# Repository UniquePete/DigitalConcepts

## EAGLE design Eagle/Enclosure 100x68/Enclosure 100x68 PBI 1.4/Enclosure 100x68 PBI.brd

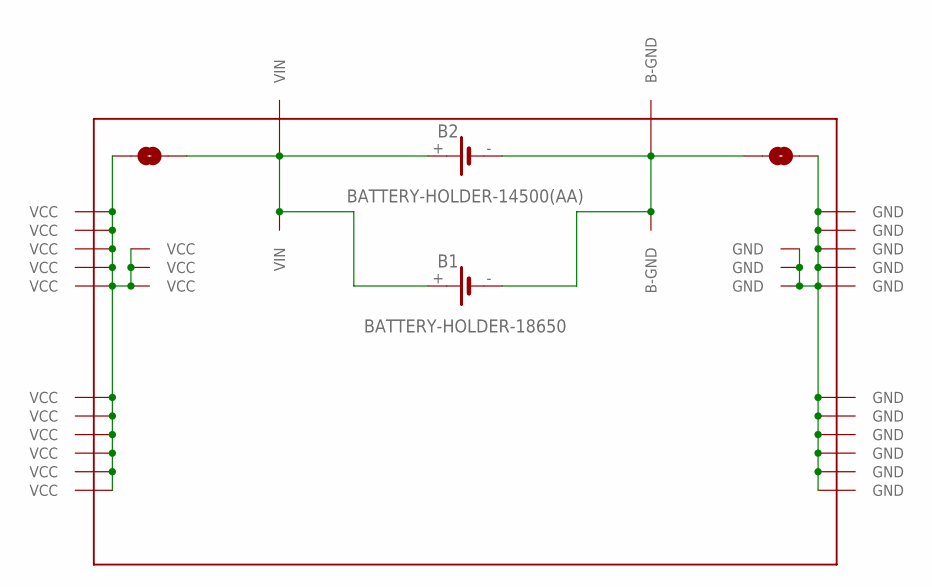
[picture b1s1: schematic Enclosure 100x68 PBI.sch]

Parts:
B1: BATTERY-HOLDER-18650; BATTERY-18650
B2: BATTERY-HOLDER-14500(AA); BATTERY-14500
P1: PROTO-34X22-BAT-SJ-MK2

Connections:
GND: P1.GND, P1.P33-13 (GND), P1.P33-14 (GND), P1.P33-15 (GND), P1.P34-05 (GND), P1.P34-06 (GND), P1.P34-07 (GND), P1.P34-08 (GND), P1.P34-09 (GND), P1.P34-10 (GND), P1.P34-13 (GND), P1.P34-14 (GND), P1.P34-15 (GND), P1.P34-16 (GND), P1.P34-17 (GND)
unnamed: B1.+, B2.+, P1.P02-17 (VIN), P1.P05-19 (VIN), P1.VIN
unnamed: B1.-, B2.-, P1.B-GND, P1.P30-19 (B-GND), P1.P33-17 (B-GND)
VCC: P1.P01-05 (VCC), P1.P01-06 (VCC), P1.P01-07 (VCC), P1.P01-08 (VCC), P1.P01-09 (VCC), P1.P01-10 (VCC), P1.P01-13 (VCC), P1.P01-14 (VCC), P1.P01-15 (VCC), P1.P01-16 (VCC), P1.P01-17 (VCC), P1.P02-13 (VCC), P1.P02-14 (VCC), P1.P02-15 (VCC), P1.VCC

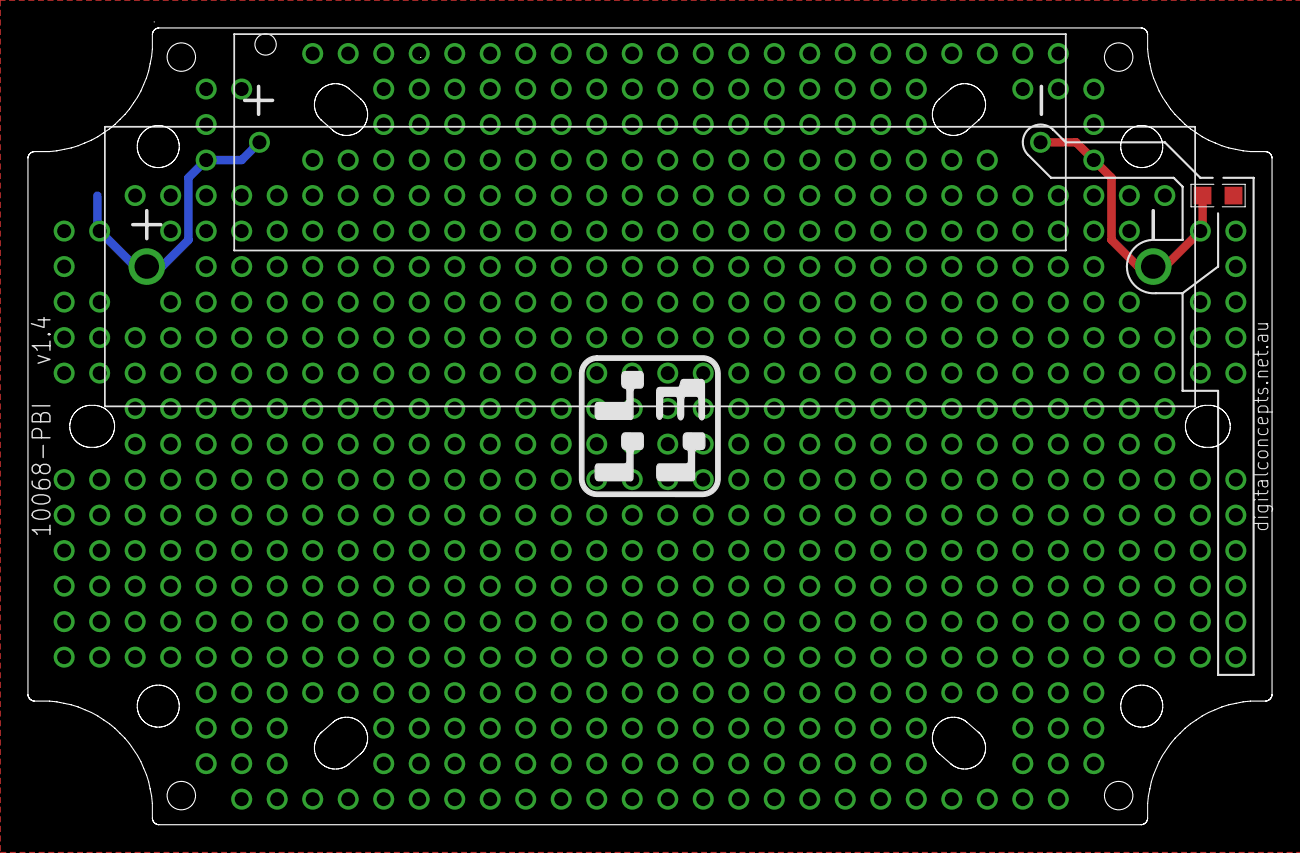
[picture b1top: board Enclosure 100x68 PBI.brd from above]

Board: 2 copper layers, 89.0 x 57.0 mm, 3 parts (0 on the bottom side), 4 nets.

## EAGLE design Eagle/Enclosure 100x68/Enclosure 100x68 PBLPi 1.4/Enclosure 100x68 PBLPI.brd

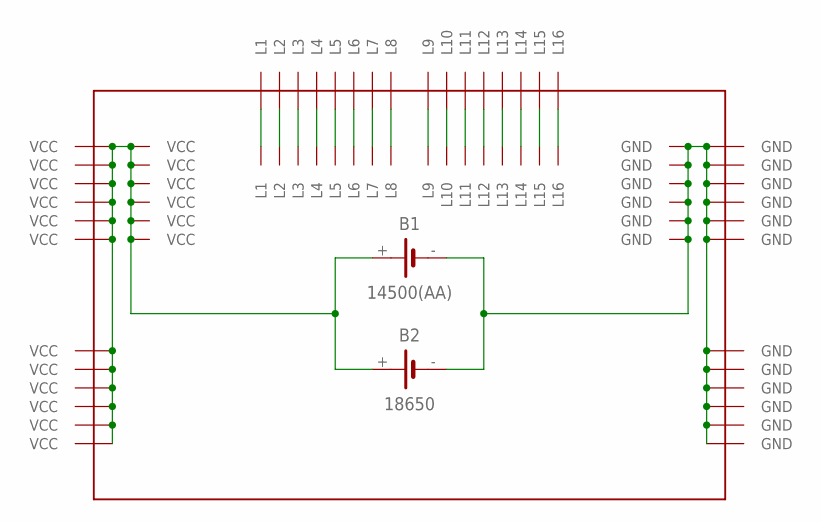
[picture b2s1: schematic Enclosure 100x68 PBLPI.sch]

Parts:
B1: 14500(AA); BATTERY-14500
B2: 18650; BATTERY-18650
P1: PROTO-34X22-BAT-PI

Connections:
GND: B1.-, B2.-, P1.P33-13 (GND), P1.P33-14 (GND), P1.P33-15 (GND), P1.P33-16 (GND), P1.P33-17 (GND), P1.P33-18 (GND), P1.P34-05 (GND), P1.P34-06 (GND), P1.P34-07 (GND), P1.P34-08 (GND), P1.P34-09 (GND), P1.P34-10 (GND), P1.P34-13 (GND), P1.P34-14 (GND), P1.P34-15 (GND), P1.P34-16 (GND), P1.P34-17 (GND), P1.P34-18 (GND)
unnamed: P1.P10-21 (L1), P1.P10-22 (L1)
unnamed: P1.P11-21 (L2), P1.P11-22 (L2)
unnamed: P1.P12-21 (L3), P1.P12-22 (L3)
unnamed: P1.P13-21 (L4), P1.P13-22 (L4)
unnamed: P1.P14-21 (L5), P1.P14-22 (L5)
unnamed: P1.P15-21 (L6), P1.P15-22 (L6)
unnamed: P1.P16-21 (L7), P1.P16-22 (L7)
unnamed: P1.P17-21 (L8), P1.P17-22 (L8)
unnamed: P1.P18-21 (L9), P1.P18-22 (L9)
unnamed: P1.P19-21 (L10), P1.P19-22 (L10)
unnamed: P1.P20-21 (L11), P1.P20-22 (L11)
unnamed: P1.P21-21 (L12), P1.P21-22 (L12)
unnamed: P1.P22-21 (L13), P1.P22-22 (L13)
unnamed: P1.P23-21 (L14), P1.P23-22 (L14)
unnamed: P1.P24-21 (L15), P1.P24-22 (L15)
unnamed: P1.P25-21 (L16), P1.P25-22 (L16)
VCC: B1.+, B2.+, P1.P01-05 (VCC), P1.P01-06 (VCC), P1.P01-07 (VCC), P1.P01-08 (VCC), P1.P01-09 (VCC), P1.P01-10 (VCC), P1.P01-13 (VCC), P1.P01-14 (VCC), P1.P01-15 (VCC), P1.P01-16 (VCC), P1.P01-17 (VCC), P1.P01-18 (VCC), P1.P02-13 (VCC), P1.P02-14 (VCC), P1.P02-15 (VCC), P1.P02-16 (VCC), P1.P02-17 (VCC), P1.P02-18 (VCC)

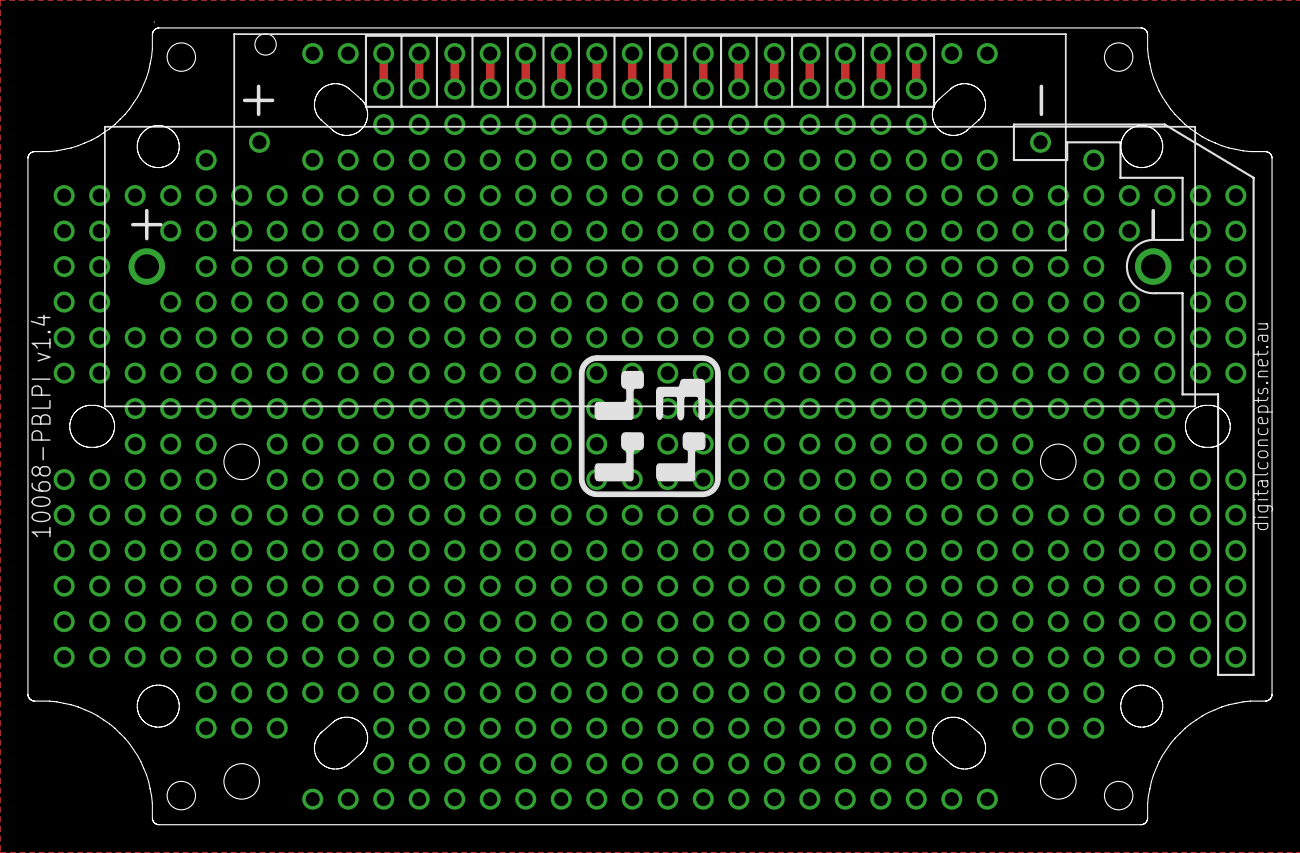
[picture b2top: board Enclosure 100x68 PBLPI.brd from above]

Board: 2 copper layers, 89.0 x 57.0 mm, 3 parts (0 on the bottom side), 18 nets.

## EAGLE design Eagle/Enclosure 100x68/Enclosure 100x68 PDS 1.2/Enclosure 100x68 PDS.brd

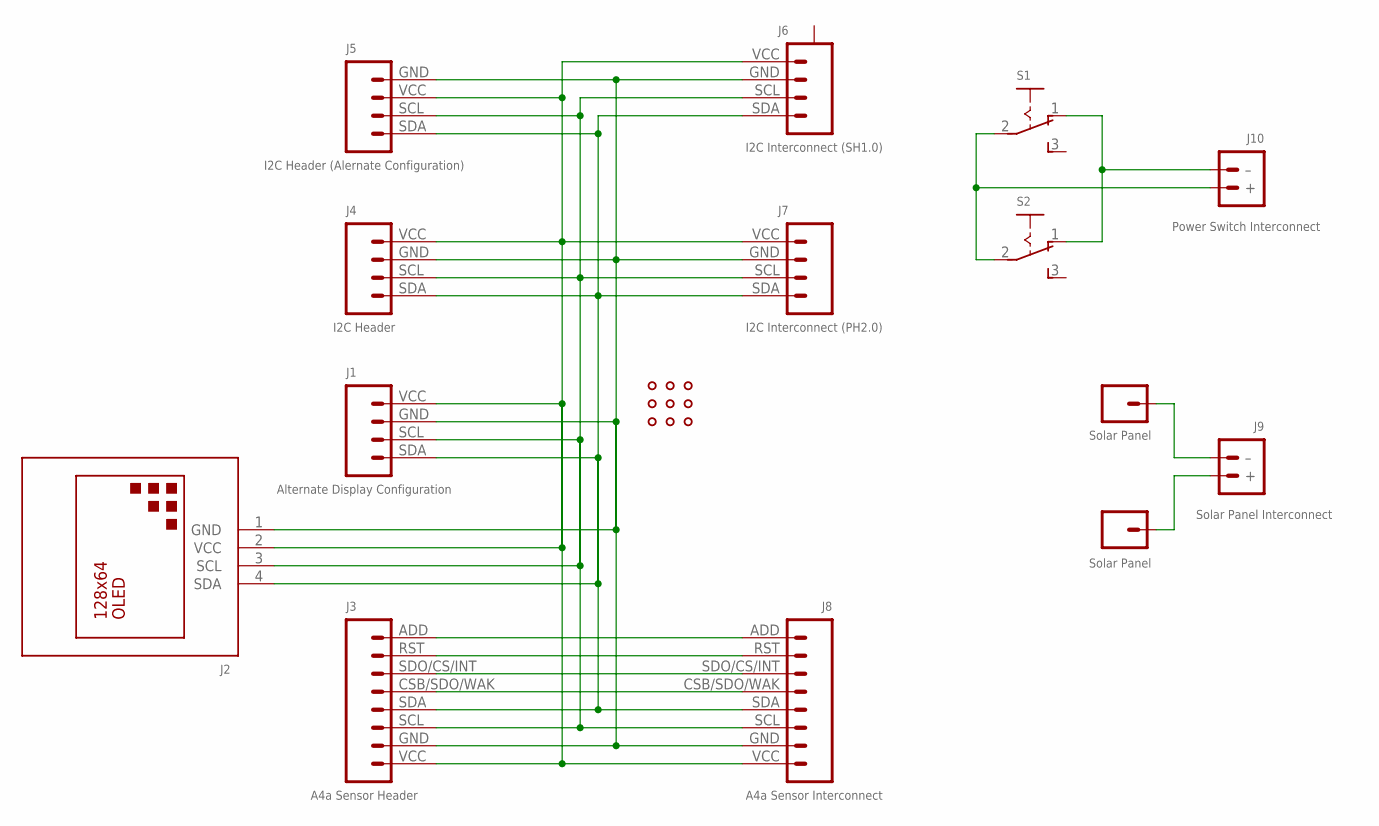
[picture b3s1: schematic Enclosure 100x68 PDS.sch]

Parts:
+: Solar Panel; PAD-SMD-GENERIC
-: Solar Panel; PAD-SMD-GENERIC
J1: Alternate Display Configuration; CONN_04-I2C
J2: DISPLAY-OLED-128X64-OFFSET-X-I2C
J3: A4a Sensor Header; CONN_08-SENSOR
J4: I2C Header; CONN_04-I2C
J5: I2C Header (Alernate Configuration); CONN_04-I2C-X
J6: I2C Interconnect (SH1.0); JST-SH1.0-4-I2C-HORIZONTAL
J7: I2C Interconnect (PH2.0); JST-PH2.0-4-HORIZONTAL
J8: A4a Sensor Interconnect; CONN_08-SENSOR
J9: Solar Panel Interconnect; JST-PH2.0-2-HORIZONTAL
J10: Power Switch Interconnect; JST-PH2.0-2-HORIZONTAL
S1, S2: SWITCH-SLIDE-SPDT; SWITCH-SPDT-PTH
U$1: PROTO-34X22-JST-DS

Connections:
GND: J1.GND (2), J2.1 (GND), J3.GND (2), J4.GND (2), J5.GND (1), J6.GND (3), J7.GND (3), J8.GND (2)
unnamed: J1.SDA (4), J2.4 (SDA), J3.SDA (4), J4.SDA (4), J5.SDA (4), J6.SDA (1), J7.SDA (1), J8.SDA (4)
unnamed: J1.SCL (3), J2.3 (SCL), J3.SCL (3), J4.SCL (3), J5.SCL (3), J6.SCL (2), J7.SCL (2), J8.SCL (3)
unnamed: J3.CSB/SDO/WAK (5), J8.CSB/SDO/WAK (5)
unnamed: J3.SDO/CS/INT (6), J8.SDO/CS/INT (6)
unnamed: J3.RST (7), J8.RST (7)
unnamed: J3.ADD (8), J8.ADD (8)
unnamed: -.P$1, J9.2 (–)
unnamed: +.P$1, J9.1 (+)
unnamed: J10.1 (+), S1.2, S2.2
unnamed: J10.2 (–), S1.1 (O), S2.1 (O)
VCC: J1.VCC (1), J2.2 (VCC), J3.VCC (1), J4.VCC (1), J5.VCC (2), J6.VCC (4), J7.VCC (4), J8.VCC (1)

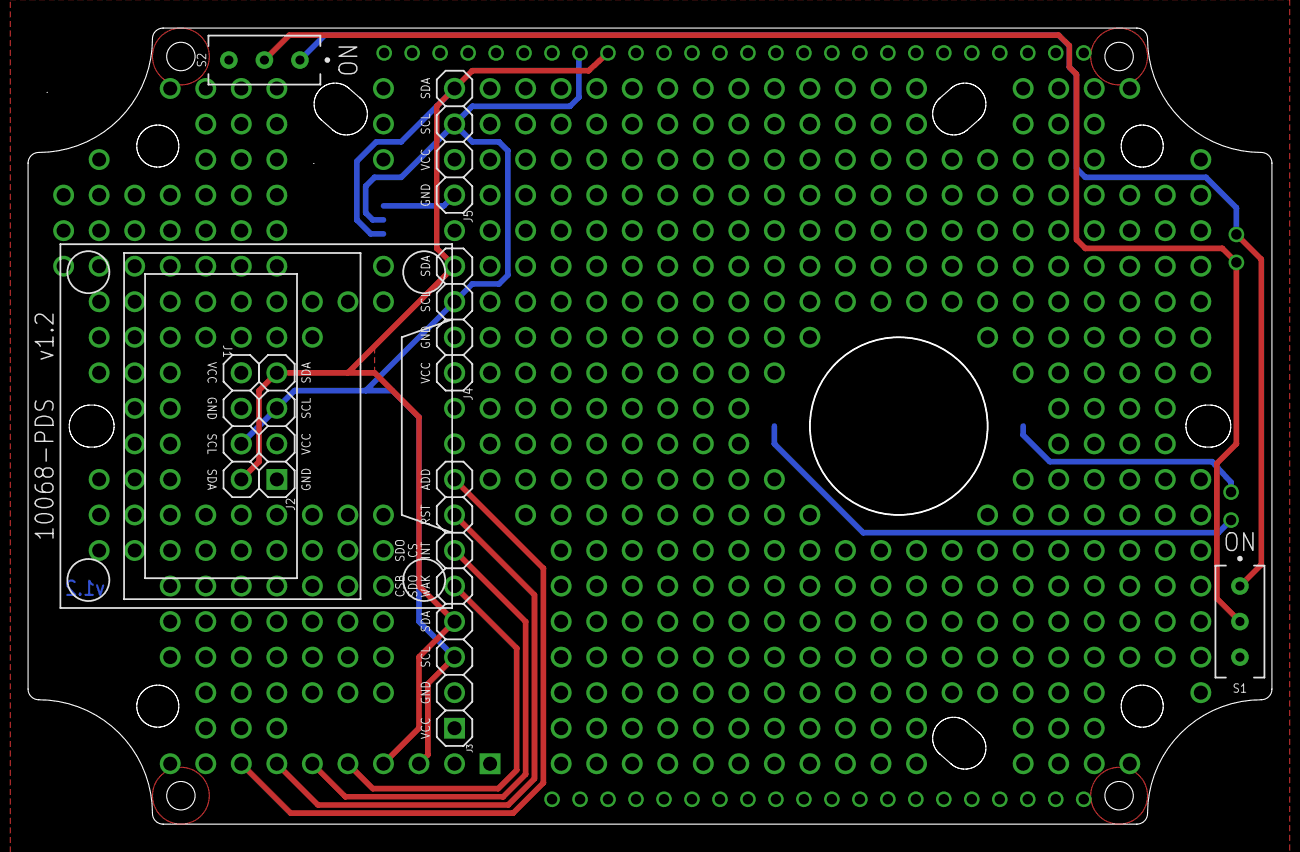
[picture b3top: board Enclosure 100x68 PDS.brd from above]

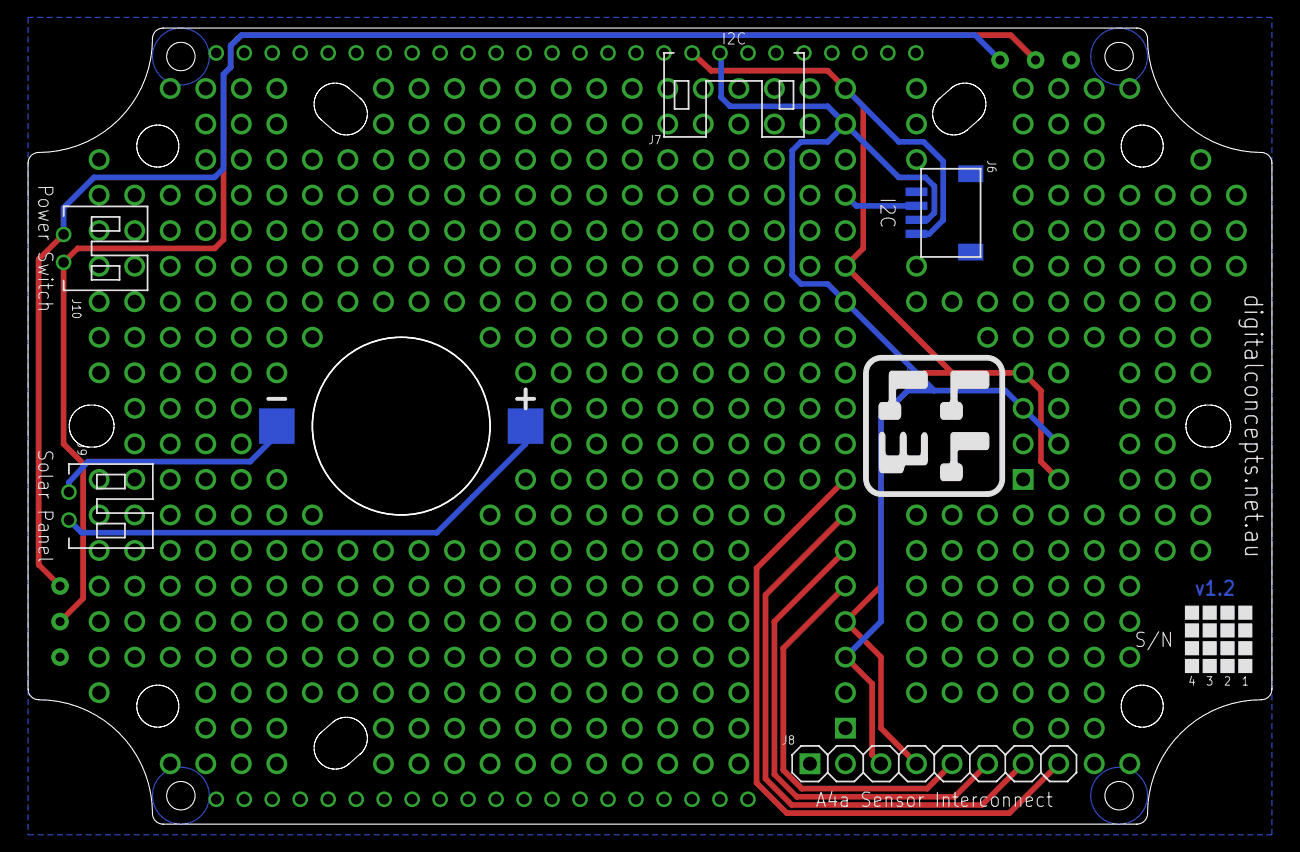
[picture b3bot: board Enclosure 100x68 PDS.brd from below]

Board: 2 copper layers, 88.9 x 56.9 mm, 15 parts (7 on the bottom side), 12 nets.
